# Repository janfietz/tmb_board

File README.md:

# tmb_board
Hardware design for [toddlerMusicBox](http://janfietz.github.io/toddlerMusicBox/) project.

# Firmware
Firmware project is hosted as [tmb_musicplayer](https://github.com/janfietz/tmb_musicplayer)

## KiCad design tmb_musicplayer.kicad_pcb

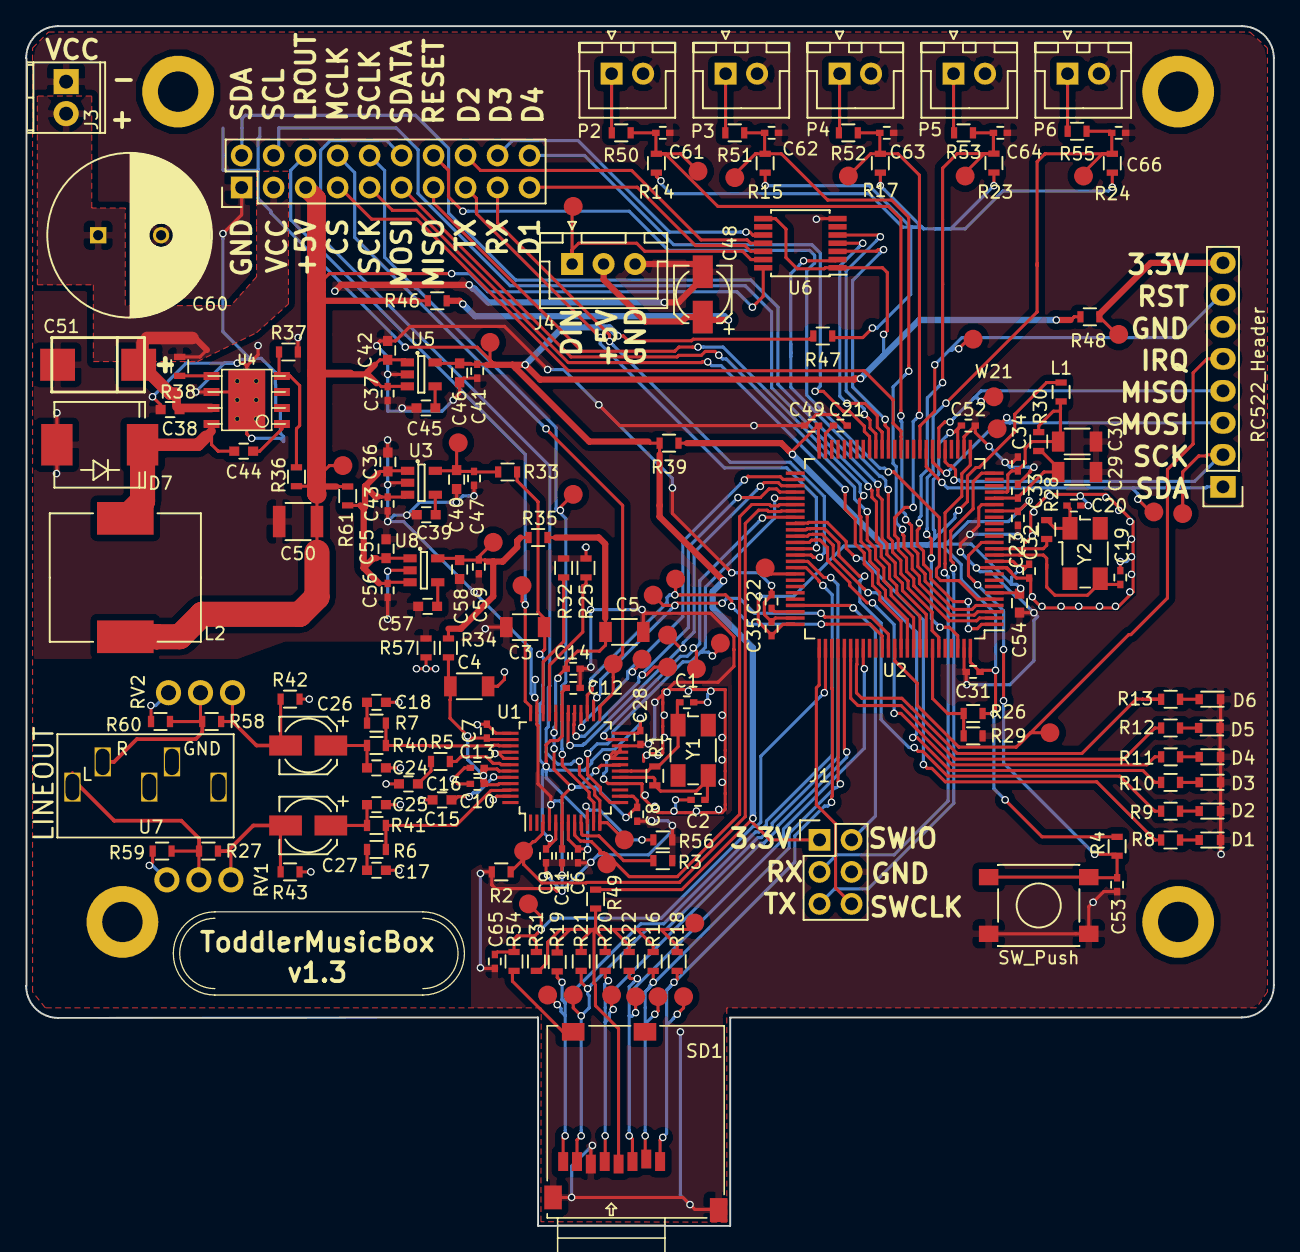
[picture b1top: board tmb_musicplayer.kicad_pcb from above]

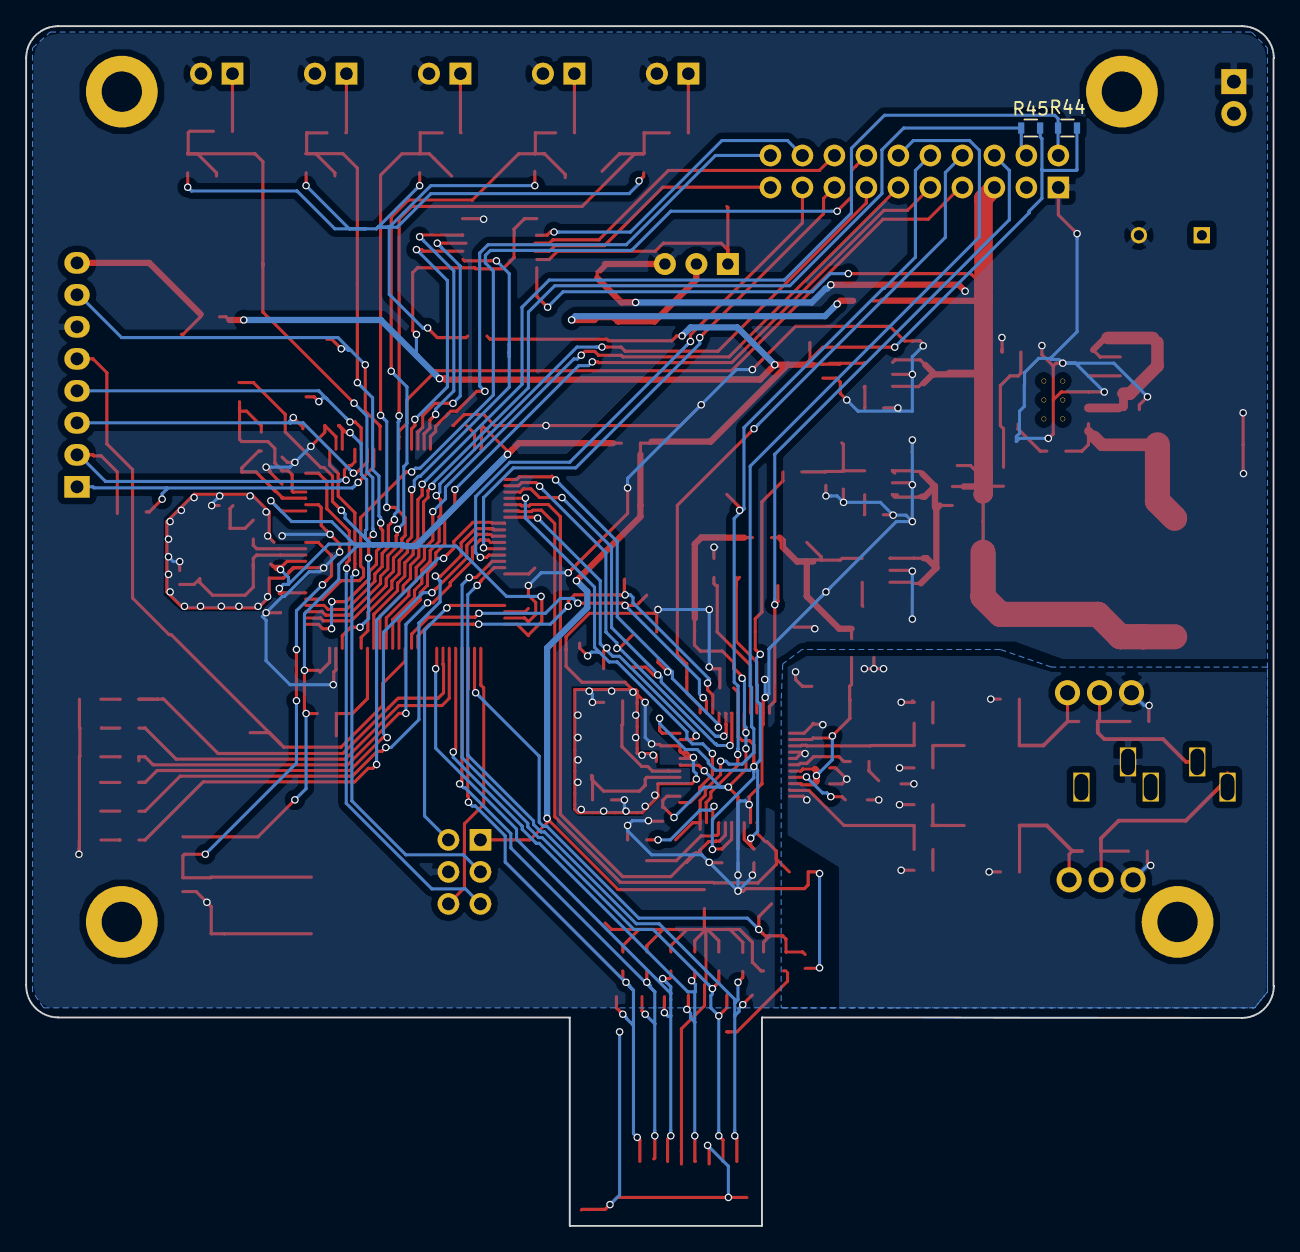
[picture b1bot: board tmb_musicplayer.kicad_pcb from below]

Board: 2 copper layers, 99.1 x 95.3 mm, 199 parts (2 on the bottom side), 123 nets.

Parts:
C1, C2, C19, C20: 15pF; C_0402
C3, C4, C5: 10uF; C_1206
C6, C7, C8, C9, C10, C11, C12, C13, C14, C23, C28, C31, C32, C33, C34, C35, C37, C41, C43, C47, C49, C52, C53, C56, C59, C61, C62, C63, C64, C65, C66: 100nF; C_0402
C15, C36, C40, C42, C46, C54, C55, C58: 1uF; C_0603
C16: 47nF; C_0603
C17, C18, C39, C44, C45, C57: 10nF; C_0603
C21, C22: 2.2uF; C_0402
C24, C25: 3.3nF; C_0603
C26, C27, C48: 10uF; c_elec_4x5.7
C29, C30: 1uF; C_1206
C38: 6.8uF; C_0603
C50: 120uF; C_1210
C51: 22uF; SM2917_POL
C60: 10uF; C_Radial_D13_L21_P5
D1: LED_Yellow; D_0603
D2: LED_Red; D_0603
D3, D5: LED_Green; D_0603
D4: LED_Orange; D_0603
D6: LED_Blue; D_0603
D7: D_Schottky_60V_5A; SMC_Standard
J1: SWD; Pin_Header_Straight_2x03
J2: RC522_Header; Pin_Header_Straight_1x08
J3: Screw_Terminal_1x02; TerminalBlock_Pheonix_MPT-2.54mm_2pol
J4: LED; JST_XH_B03B-XH-A_03x2.50mm_Straight
L1: FCM1608KF-601T03; R_0603
L2: 33uH; Inductor_Wurth_HCM-1240
P2: VolDown; JST_XH_B02B-XH-A_02x2.50mm_Straight
P3: Prev; JST_XH_B02B-XH-A_02x2.50mm_Straight
P4: Play; JST_XH_B02B-XH-A_02x2.50mm_Straight
P5: Next; JST_XH_B02B-XH-A_02x2.50mm_Straight
P6: VolUp; JST_XH_B02B-XH-A_02x2.50mm_Straight
P7: CONN_02X10; Pin_Header_Straight_2x10
R1: 1M; R_0603
R2, R3, R14, R15, R17, R23, R24, R25, R31, R32, R42, R43, R56: 100k; R_0603
R4, R16, R18, R19, R20, R21, R22: 10k; R_0603
R5: 10R; R_0603
R6, R7: 20R; R_0603
R8, R9, R10, R11, R12, R13: 680; R_0603
R26, R59, R60: NA; R_0603
R27, R33, R34, R35, R36, R39, R46, R47, R48, R49, R57, R58, R61: 0; R_0603
R28: 220; R_0603
R29: 510; R_0603
R30: 47; R_0603
R37, R50, R51, R52, R53, R54, R55: 1k; R_0603
R38: 470k; R_0603
R40, R41: 470; R_0603
R44, R45: 4.7k; R_0603
RV1, RV2: 10k; Potentiometer_WirePads_Small_nosilk
SD1: MICROSD_CARD_RIGHT; MF_Connectors-MF-MICROSD
SW1: SW_Push; SW_SPST_PTS645
U1: VS1053; LQFP-48_7x7mm_Pitch0.5mm
U2: STM32F407VGTx; LQFP-100_14x14mm_Pitch0.5mm
U3: LD3985M18R; SOT-23-5
U4: LM22676QMRX-5.0; HSOP-8
U5, U8: LD3985M33R; SOT-23-5
U6: TXB0104; TSSOP-14_4.4x5mm_Pitch0.65mm
U7: LINEOUT; AUDIO_JACK
W1: DREQ; Measurement_Point_Round-SMD-Pad_Small
W2: RX; Measurement_Point_Round-SMD-Pad_Small
W3: TX; Measurement_Point_Round-SMD-Pad_Small
W4, W21: MISO; Measurement_Point_Round-SMD-Pad_Small
W5, W20: MOSI; Measurement_Point_Round-SMD-Pad_Small
W6, W10: SCLK; Measurement_Point_Round-SMD-Pad_Small
W7: XCS; Measurement_Point_Round-SMD-Pad_Small
W8: SDATA; Measurement_Point_Round-SMD-Pad_Small
W9: XDCS; Measurement_Point_Round-SMD-Pad_Small
W11: MCLK; Measurement_Point_Round-SMD-Pad_Small
W12: XRESET; Measurement_Point_Round-SMD-Pad_Small
W13: LROUT; Measurement_Point_Round-SMD-Pad_Small
W14: LEDDIN; Measurement_Point_Round-SMD-Pad_Small
W15: BTNDO; Measurement_Point_Round-SMD-Pad_Small
W16: SDA; Measurement_Point_Round-SMD-Pad_Small
W17: RESET; Measurement_Point_Round-SMD-Pad_Small
W18: SCK; Measurement_Point_Round-SMD-Pad_Small
W19: IRQ; Measurement_Point_Round-SMD-Pad_Small
W22, W27: 3V3; Measurement_Point_Round-SMD-Pad_Small
W23: BTNPR; Measurement_Point_Round-SMD-Pad_Small
W24: BTNPL; Measurement_Point_Round-SMD-Pad_Small
W25: D2; Measurement_Point_Round-SMD-Pad_Small
W26: D1; Measurement_Point_Round-SMD-Pad_Small
W28: D0; Measurement_Point_Round-SMD-Pad_Small
W29: D3; Measurement_Point_Round-SMD-Pad_Small
W30: CD; Measurement_Point_Round-SMD-Pad_Small
W31: CMD; Measurement_Point_Round-SMD-Pad_Small
W32: BTNNE; Measurement_Point_Round-SMD-Pad_Small
W33: SD_CD; Measurement_Point_Round-SMD-Pad_Small
W34: BTNUP; Measurement_Point_Round-SMD-Pad_Small
W35, W38: 3.3V; Measurement_Point_Round-SMD-Pad_Small
W36: 1V8; Measurement_Point_Round-SMD-Pad_Small
W37: 5V; Measurement_Point_Round-SMD-Pad_Small
W39: MCO1; Measurement_Point_Round-SMD-Pad_Small
Y1: 12.288 Mhz; Crystal_SMD_ABM3B
Y2: 8MHz; Crystal_SMD_ABM3B

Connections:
+1V8: C40.1, C47.1, R33.2, U3.5, W36.1
+3.3VA: C58.1, C59.1, R34.2, R35.2, U8.5, W38.1
+3V3: C41.1, C46.1, J1.1, R39.2, R44.1, R45.1, R47.2, R48.1, R49.1, U5.5, U6.1, U6.8, W35.1
+5V: C37.1, C42.1, C50.1, L2.2, P7.5, R36.2, R46.1, R61.2, U5.1, U5.3, U6.14, W37.1
/AMP_LROUT: P7.6, U1.36, W13.1
/AMP_MCLK: P7.8, U1.25, W11.1
/AMP_SCLK: P7.10, U1.11, W10.1
/AMP_SDIN: P7.12, U1.12, W8.1
/Externals/EXT_DIO1_5V: P7.19, U6.12
/Externals/EXT_DIO2_5V: P7.16, U6.11
/Externals/EXT_DIO3_5V: P7.18, U6.10
/Externals/LED_DATA_5V: J4.1, U6.13, W14.1
/Main/NRST: C53.1, R4.1, SW1.1, U2.14
/Main/PA8: U2.67, W39.1
/Main/VDDA: C30.1, C34.2, L1.2, R30.2, U2.22
/Main/VREF+: C29.1, C33.1, R30.1, U2.21
/PA2: J1.5, U2.25
/PA3: J1.3, U2.26
/PA5: J2.2, U2.30, W18.1
/PA6: J2.4, U2.31, W21.1
/PA7: J2.3, U2.32, W20.1
/PA13: J1.2, U2.72
/PA14: J1.6, U2.76
/PA15: C65.1, R31.2, R54.2, U2.77, W33.1
/PB2: P7.7, U2.37
/PB3: P7.9, U2.89
/PB4: P7.13, U2.90
/PB5: P7.11, U2.91
/PB6: P7.4, R45.2, U2.92
/PB7: P7.2, R44.2, U2.93
/PB8: U2.95, U6.2
/PB13: U1.28, U2.52, W6.1
/PB14: U1.30, U2.53, W4.1
/PB15: U1.29, U2.54, W5.1
/PC4: J2.1, U2.33, W16.1
/PC5: J2.7, U2.34, W17.1
/PC6: P7.15, U2.63
/PC7: P7.17, U2.64
/PC8: R21.2, SD1.7, U2.65, W28.1
/PC9: R19.2, SD1.8, U2.66, W26.1
/PC10: R18.2, SD1.1, U2.78, W25.1
/PC11: R16.2, SD1.2, U2.79, W29.1
/PC12: R20.2, SD1.5, U2.80, W30.1
/PD0: R12.2, U2.81
/PD1: R13.2, U2.82
/PD2: R22.2, SD1.3, U2.83, W31.1
/PD5: U1.27, U2.86, W3.1
/PD6: U1.26, U2.87, W2.1
/PD7: J2.5, U2.88, W19.1
/PD8: U1.13, U2.55, W9.1
/PD9: U1.8, U2.56, W1.1
/PD10: R2.1, U1.3, U2.57, W12.1
/PD11: U1.23, U2.58, W7.1
/PD12: R8.2, U2.59
/PD13: R9.2, U2.60
/PD14: R10.2, U2.61
/PD15: R11.2, U2.62
/PE1: C66.1, R24.2, R55.2, U2.98, W34.1
/PE2: C64.1, R23.2, R53.2, U2.1, W32.1
/PE3: C63.1, R17.2, R52.2, U2.2, W24.1
/PE4: C62.1, R15.2, R51.2, U2.3, W23.1
/PE5: C61.1, R14.2, R50.2, U2.4, W15.1
/PE6: P7.14, U2.5
/PE8: U2.39, U6.3
/PE9: U2.40, U6.4
/PE10: U2.41, U6.5
/PE11: P7.20, U2.42
/Power/+5V_VLSI: C36.1, C43.1, C55.1, C56.1, R61.1, U3.1, U3.3, U8.1, U8.3
/VS1053/LEFT: R6.1, R41.2, U1.46
/VS1053/RIGHT: R7.2, R40.2, U1.39
ACVDD: C4.1, C7.1, C10.1, C13.1, R34.1, U1.38, U1.43, U1.45
CVDD: C3.1, C6.1, C9.1, C12.1, C28.1, R33.1, U1.5, U1.7, U1.24, U1.31
GND: C1.2, C2.2, C3.2, C5.2, C6.2, C8.2, C9.2, C11.2, C12.2, C14.2, C19.2, C20.2, C21.2, C22.2, C23.2, C28.2, C29.2, C30.2, C31.2, C32.2, C33.2, C34.1, C35.2, C36.2, C37.2, C38.2, C39.2, C40.2, C41.2, C42.2, C43.2, C45.2, C46.2, C47.2, C48.2, C49.2, C50.2, C51.2, C52.2, C53.2, C54.2, C55.2, C56.2, C57.2, C58.2, C59.2, C60.2, C61.2, C62.2, C63.2, C64.2, C65.2, C66.2, D1.1, D2.1, D3.1, D4.1, D5.1, D6.1, D7.2, J1.4, J2.6, J3.1, J4.3, P2.2, P3.2, P4.2, P5.2, P6.2, P7.1, R2.2, R3.2, R25.2, R29.2, R32.2, R37.1, R56.2, R57.2, SD1.6, SD1.G0, SD1.G1, SW1.2, U1.4, U1.16, U1.20, U1.21, U1.22, U1.35, U2.10, U2.20, U2.27, U2.74, U2.99, U3.2, U4.6, U4.9, U5.2, U6.7, U8.2
GNDA: C4.2, C7.2, C10.2, C13.2, C15.2, C16.1, C17.2, C18.1, C24.2, C25.2, R42.1, R43.1, R57.1, R59.1, R60.2, RV1.3, RV2.1, U1.37, U1.40, U1.41, U1.47, U7.3
IOVDD: C5.1, C8.1, C11.1, C14.1, R35.1, U1.6, U1.14, U1.19, U1.32
unnamed: C1.1, R1.2, U1.18, Y1.1
unnamed: C2.1, R1.1, U1.17, Y1.2
unnamed: C15.1, U1.44
unnamed: C16.2, R5.1
unnamed: C17.1, R6.2
unnamed: C18.2, R7.1
unnamed: C19.1, U2.12, Y2.2
unnamed: C20.1, R28.2, Y2.1
unnamed: C21.1, U2.49
unnamed: C22.1, U2.73
unnamed: C24.1, C26.1, R40.1
unnamed: C25.1, C27.1, R41.1
unnamed: C26.2, R42.2, R58.1, RV2.3
unnamed: C27.2, R27.2, R43.2, RV1.1
unnamed: C39.1, U3.4
unnamed: C44.1, D7.1, L2.1, U4.8
unnamed: C44.2, U4.1
unnamed: C45.1, U5.4
unnamed: C48.1, J4.2, R46.2
unnamed: C57.1, U8.4
unnamed: D1.2, R8.1
unnamed: D2.2, R9.1
unnamed: D3.2, R10.1
unnamed: D4.2, R11.1
unnamed: D5.2, R12.1
unnamed: D6.2, R13.1
unnamed: J2.8, R48.2, W22.1
unnamed: P2.1, R50.1
unnamed: P3.1, R51.1
unnamed: P4.1, R52.1
unnamed: P5.1, R53.1
unnamed: P6.1, R55.1
unnamed: R3.1, U1.9
unnamed: R5.2, U1.42
unnamed: R14.1, R15.1, R17.1, R23.1, R24.1, R47.1
unnamed: R16.1, R18.1, R19.1, R20.1, R21.1, R22.1, R31.1, R49.2, SD1.4, W27.1
unnamed: R25.1, U1.33
unnamed: R26.1, R29.1, U2.94
unnamed: R27.1, R59.2, RV1.2, U7.1
unnamed: R28.1, U2.13
unnamed: R32.1, U1.34
unnamed: R36.1, R37.2, U4.4
unnamed: R38.2, U4.5
unnamed: R54.1, SD1.9
unnamed: R56.1, U1.10
unnamed: R58.2, R60.1, RV2.2, U7.2
VCC: C38.1, C51.1, C60.1, J3.2, P7.3, R38.1, U4.7
VDD: C23.1, C31.1, C32.1, C35.1, C49.1, C52.1, C54.1, L1.1, R4.2, R26.2, R39.1, U2.6, U2.11, U2.19, U2.28, U2.50, U2.75, U2.100

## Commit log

2017-09-18 Add CC-BY-SA-4.0
2017-09-18 remove library links
2017-09-18 VS1053: use kicad audio jack component
2017-09-24 Use smd oscilator Add testpoints Use different power networks
2017-09-25 new layout
2017-09-27 Macrofab sd card footprint
2017-10-07 Finished new layout
2017-10-07 add gerber export
2017-10-07 increased Version
2017-10-14 Remove 3. LDO some improvements
2017-10-16 some minor improvements
2017-10-22 Version 1.2
2017-10-23 Fixed footprint of L1
2018-02-28 gerber: new plots
2018-02-28 Changed butten connectors
